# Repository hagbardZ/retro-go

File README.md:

# Table of contents
- [Description](#description)
- [Installation](#installation)
- [Usage](#usage)
- [Issues](#issues)
- [Development](#development)
- [Acknowledgements](#acknowledgements)
- [License](#license)

# Description
Retro-Go is a firmware to play retro games on ESP32-based devices (officially supported are
ODROID-GO and MRGC-G32, check [this list for other devices](components/retro-go/README.md)).
The project consists of a launcher and half a dozen applications that have been heavily
optimized to reduce their cpu, memory, and flash needs without reducing compatibility!

### Supported systems:
- Nintendo: **NES, SNES (slow), Gameboy, Gameboy Color, Game & Watch**, **Gameboy Advance**
- Sega: **SG-1000, Master System, Mega Drive / Genesis, Game Gear**
- Coleco: **Colecovision**
- NEC: **PC Engine**
- Atari: **Lynx**, **Atari 2600**
- Others: **DOOM** (including mods!), **Commodore 64**, **Commodore Amiga**, **Duke Nukem 3D**, **Quake**, **MSX**, **Tomb Raider**, **Super Mario 64**, **Outrun**, **Classicube**, **Open Tyrian**, **Playstation**, **Mario Kart 64**, **Quake 2**, **MP3 Player**, **Celeste**

### Retro-Go features:
- In-game menu
- Favorites and recently played
- GB color palettes, RTC adjust and save
- NES color palettes, PAL roms, NSF support
- More emulators and applications
- Scaling and filtering options
- Better performance and compatibility
- Turbo Speed/Fast forward
- Customizable launcher
- Cover art and save state previews
- Multiple save slots per game
- Wifi file manager
- And more!

### Screenshots

# Installation

### ODROID-GO
  1. Download `retro-go_1.x_odroid-go.fw` from the [release page](https://github.com/ducalex/retro-go/releases/) and copy it to `/odroid/firmware` on your sdcard.
  2. Power up the device while holding down B.
  3. Select retro-go in the files list and flash it.

### MyRetroGameCase G32 (GBC)
  1. Download `retro-go_1.x_mrgc-g32.fw` from the [release page](https://github.com/ducalex/retro-go/releases/) and copy it to `/espgbc/firmware` on your sdcard.
  2. Power up the device while holding down MENU (the volume knob).
  3. Select retro-go in the files list and flash it.

### Other devices
  1. Download the .img for your device from the [release page](https://github.com/ducalex/retro-go/releases/).
  2. Connect your device to a computer with a USB cable.
  3. Flash the image with esptool:
     - [Command line](https://github.com/espressif/esptool/releases/): Run `esptool.py write_flash --flash_size detect 0x0 retro-go_*.img`
     - [Web version](https://espressif.github.io/esptool-js/): Connect your device, click Erase Flash, then select your .img file and set address to 0x0, finally click Program)

Your particular device may require extra steps (like holding a button during power up) or different esptool flags or a special cable. If the above steps fail, you might need to ask the manufacturer for instructions on how to flash new firmware!

If your device is not already supported or if a prebuilt version isn't available for it you can check the [development section](#Development) for more information on how to build for your device.

# Usage

## Game covers / artwork
Game covers should be placed in the `romart` folder at the base of your sd card. You can obtain a pre-made pack [here](https://github.com/ducalex/retro-go-covers). Retro-Go is also compatible with the older Go-Play romart pack.

You can add missing cover art by creating a PNG image (160x168, 8bit). Two naming schemes are supported:
- Filename-based: `/romart/nes/Super Mario.png` (notice the rom extension is *not* included)
- CRC32-based: `/romart/nes/A/ABCDE123.png` where `nes` is the same as the rom folder, and `ABCDE123` is the CRC32 of the game (press A -> Properties in the launcher to find it), and `A` is the first character of the CRC32

_Note: CRC32-based, which is what is used in the pre-made pack, is much slower than name-based! This type is useful because filenames vary greatly despite having identical CRCs, but if you generate your own art I suggest you use filename-based format and delete all CRC-based art from your SD Card to improve responsiveness._

## BIOS files
Some emulators support loading a BIOS. The files should be placed as follows:
- GB: `/retro-go/bios/gb_bios.bin`
- GBC: `/retro-go/bios/gbc_bios.bin`
- FDS: `/retro-go/bios/fds_bios.bin`
- MSX: In folder `/retro-go/bios/msx/` put: `MSX.ROM` `MSX2.ROM` `MSX2EXT.ROM` `MSX2P.ROM` `MSX2PEXT.ROM` `FMPAC.ROM` `DISK.ROM` `MSXDOS2.ROM` `PAINTER.ROM` `KANJI.ROM`

## Game & Watch
The roms must be packed with [LCD-Game-Shrinker](https://github.com/bzhxx/LCD-Game-Shrinker) and a tutorial can be [found here](https://gist.github.com/DNA64/16fed499d6bd4664b78b4c0a9638e4ef).

## Wifi
To use wifi you will need to create a `/retro-go/config/wifi.json` config file. You can define up to 4 different networks, then selectable in the menu. Its content should look like this:

````json
{
  "ssid0": "my-network",
  "password0": "my-password",
  "ssid1": "my-other-network",
  "password1": "my-password",
  "ssid2": "my-third-network",
  "password2": "my-password",
  "ssid3": "my-last-network",
  "password3": "my-password"
}
````

### Time synchronization
Time synchronization happens in the launcher immediately after a successful connection to the network.
This is done via NTP by contacting `pool.ntp.org` and cannot be disabled at this time.
Timezone can be configured in the launcher's options menu.

### File manager
You can find the IP of your device in the *about* menu of retro-go. Then on your PC navigate to
http://192.168.x.x/ to access the file manager.

## External DAC (headphones)

Retro-Go supports [the external DAC mod for the ODROID-GO](https://github.com/backofficeshow/odroid-go-audio-hat)
which allows high quality audio through headphones. You can switch to it in the menu `Audio Out: Ext DAC`.

<details>
  <summary>Pinout</summary>

  | GO PIN | PCM5102A PIN |
  |--------|---------|
  | 1 | GND |
  | 2 | - |
  | 3 | LCK |
  | 4 | DIN |
  | 5 | BCK |
  | 6 | VIN |
  | 7 | - |
  | 8 | - |
  | 9 | - |
  | 10 | - |
</details>

# Issues

### Black screen / Boot loops
Retro-Go typically detects and resolves application crashes and freezes automatically. However, if you do
get stuck in a boot loop, you can hold `DOWN` while powering up the device to return to the launcher.

### Sound quality
The volume isn't correctly attenuated on the GO, resulting in upper volume levels that are too loud and
lower levels that are distorted due to DAC resolution. A quick way to improve the audio is to cut one
of the speaker wire and add a `33 Ohm (or thereabout)` resistor in series. Soldering is better but not
required, twisting the wires tightly will work just fine.
[A more involved solution can be seen here.](https://wiki.odroid.com/odroid_go/silent_volume)
Alternatively you can use the headphones DAC mod mentioned earlier in this document.

### Game Boy SRAM *(aka Save/Battery/Backup RAM)*
In Retro-Go, save states will provide you with the best and most reliable save experience. That being said, please
read on if you need or want SRAM saves. The SRAM format is compatible with VisualBoyAdvance so it may be used to
import or export saves.

You can configure automatic SRAM saving in the options menu. A longer delay will reduce stuttering at the cost
of losing data when powering down too quickly. Also note that when *resuming* a game, Retro-Go will give priority
to a save state if present.

### ZIP files
Most Retro-Go applications now support ZIP files. ZIP archives should contain only one ROM file and nothing else. ZIP support also depends on available memory and larger ROMs may fail to load on some devices unfortunately.

# Development
If you wish to build or modify Retro-Go, you can find help in the following documents:

- Build instructions in [BUILDING.md](BUILDING.md)
- Theming instructions [THEMING.md](THEMING.md)
- Porting instructions in [PORTING.md](PORTING.md)
- Translating instructions in [LOCALIZATION.md](LOCALIZATION.md)

# Acknowledgements
- The NES/GBC/SMS emulators and base library were originally from the "Triforce" fork of the [official Go-Play firmware](https://github.com/othercrashoverride/go-play) by crashoverride, Nemo1984, and many others.
- The design of the launcher was originally inspired/copied from [pelle7's go-emu](https://github.com/pelle7/odroid-go-emu-launcher).
- PCE-GO is a fork of [HuExpress](https://github.com/kallisti5/huexpress) and [pelle7's port](https://github.com/pelle7/odroid-go-pcengine-huexpress/) was used as reference.
- The Lynx emulator is a port of [libretro-handy](https://github.com/libretro/libretro-handy).
- The SNES emulator is a port of [Snes9x 2005](https://github.com/libretro/snes9x2005).
- The DOOM engine is a port of [PrBoom 2.5.0](http://prboom.sourceforge.net/).
- The Genesis emulator is a port of [Gwenesis](https://github.com/bzhxx/gwenesis/) by bzhxx.
- The Game & Watch emulator is a port of [lcd-game-emulator](https://github.com/bzhxx/lcd-game-emulator) by bzhxx.
- The MSX emulator is a port of [fMSX](https://fms.komkon.org/fMSX/) by Marat Fayzullin.
- PNG support is provided by [lodepng](https://github.com/lvandeve/lodepng/).
- PCE cover art is from [Christian_Haitian](https://github.com/christianhaitian).
- Some icons from [Rokey](https://iconarchive.com/show/seed-icons-by-rokey.html).
- Background images from [es-theme-gbz35](https://github.com/rxbrad/es-theme-gbz35).
- Special thanks to [RGHandhelds](https://www.rghandhelds.com/) and [MyRetroGamecase](https://www.myretrogamecase.com/) for sending me a [G32](https://www.myretrogamecase.com/products/game-mini-g32-esp32-retro-gaming-console-1) device.
- The [ODROID-GO](https://forum.odroid.com/viewtopic.php?f=159&t=37599) community for encouraging the development of retro-go!

# License
Everything in this project is licensed under the [GPLv2 license](COPYING) with the exception of the following components:
- fmsx/components/fmsx (MSX Emulator, custom non-commercial license)
- handy-go/components/handy (Lynx emulator, zlib)

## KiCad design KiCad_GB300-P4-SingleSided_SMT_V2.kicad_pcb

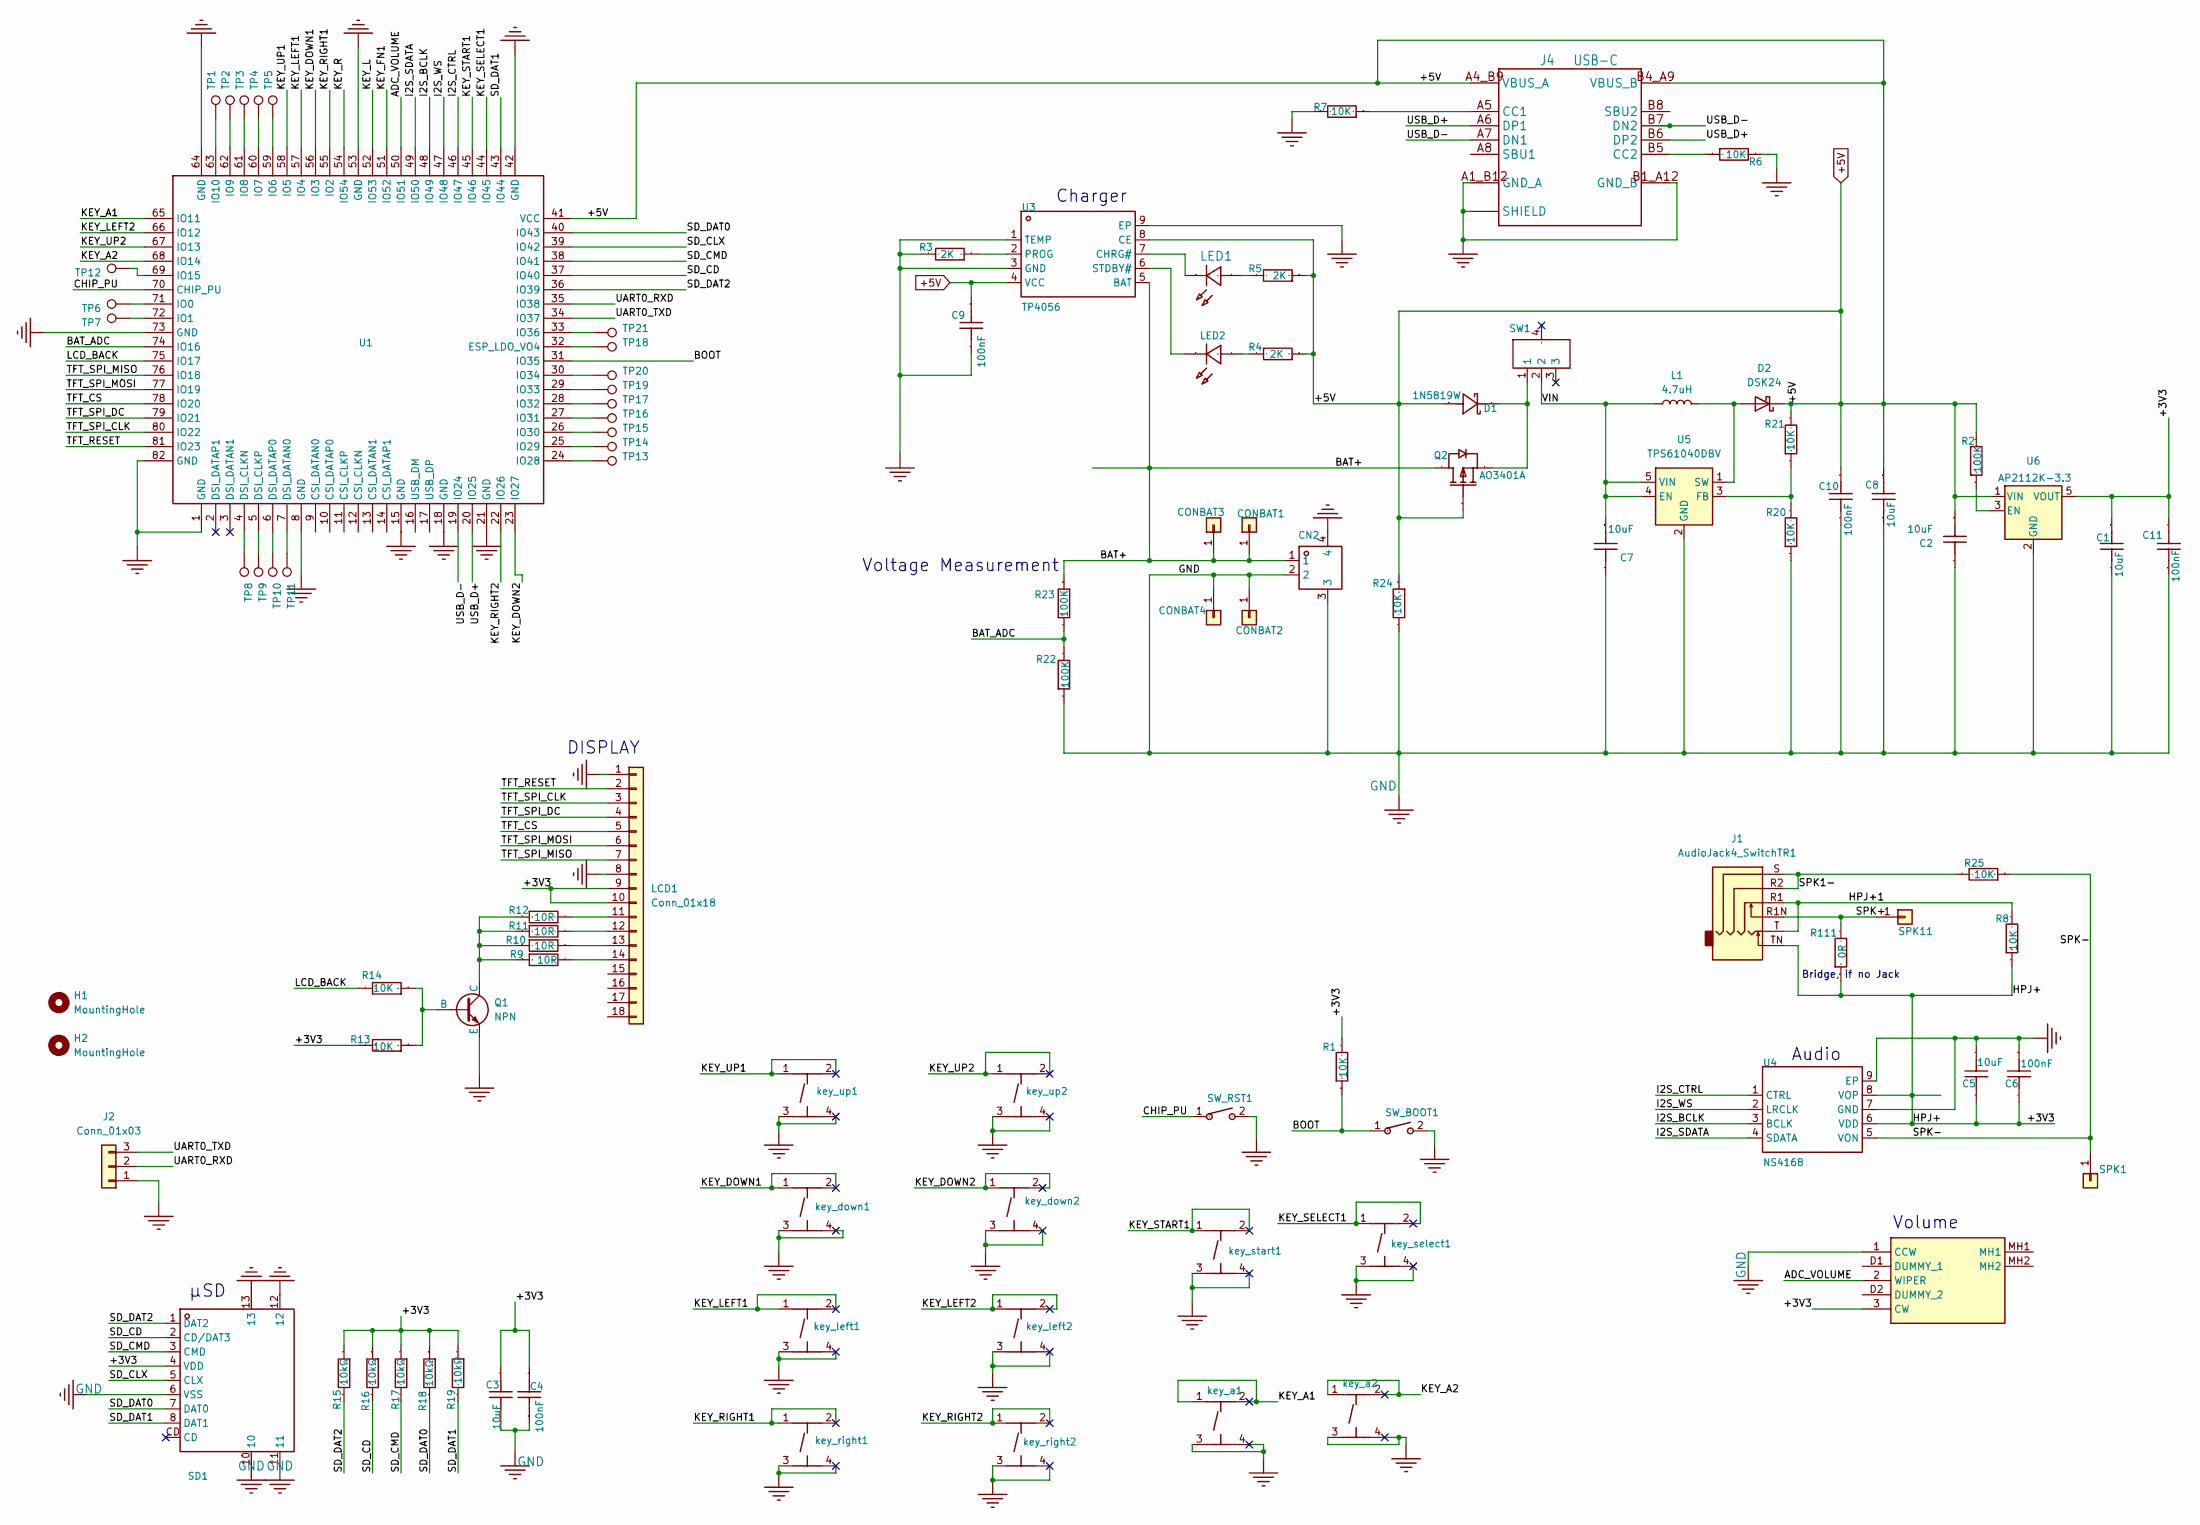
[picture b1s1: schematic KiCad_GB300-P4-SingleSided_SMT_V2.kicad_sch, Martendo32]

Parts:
C1, C2, C5: 10uF; 0603; Manufacturer Part CL10A106MA8NRNC; LCSC Part Name 10uF ±20% 25V
C3: 10uF; 0603; Manufacturer Part CGA0603X5R106K100JT; LCSC Part Name 10uF ±10% 10V
C4: 100nF; 0603; Manufacturer Part CGA0603X7R104K500JT; LCSC Part Name 100nF ±10% 50V
C6, C11: 100nF; 0603; Manufacturer Part CL10A106MA8NRNC; LCSC Part Name 10uF ±20% 25V
C7, C8: 10uF; 0603
C9, C10: 100nF; 0603
CN2: ZX-MX1.25-2PWT; CONN-SMD_2P-P1.25_D125F2W1-2W2P43; Manufacturer Part ZX-MX1.25-2PWT; LCSC Part Name 1x2P 间距:1.25mm 卧贴
CONBAT1, CONBAT2: Conn_01x01; PinHeader_1x01_P2.54mm_Vertical
CONBAT3, CONBAT4: Conn_01x01; TestPoint_Pad_3.0x3.0mm
D1: 1N5819W; SOD-123_L2.7-W1.6-LS3.7-RDaaa; Manufacturer Part 1N5819W; LCSC Part Name 电压:40V 电流:350mA
D2: DSK24; SOD-123FL_L2.7-W1.8-LS3.8-RD
H1, H2: MountingHole; MountingHole_5mm
J1: AudioJack4_SwitchTR1; AUDIO-SMD_HOOYA_PJ-242a
J2: Conn_01x03; PinSocket_1x03_P2.54mm_Vertical
J4: USB-C; AMPHENOL_GSB1C41110SSHR
L1: 4.7uH; IND-SMD_L2.5-W2.0_MHCH252012A
LCD1: Conn_01x18; ILI9341-2.8a
LED1: LED0603-RD_GREEN
LED2: LED0603-RD_RED
Q1: NPN; SOT-23-3_L2.9-W1.6-P1.90-LS2.8-BRaaa
Q2: AO3401A; SOT-23-3_L2.9-W1.6-P1.90-LS2.8-BR; Manufacturer Part AO3401A; LCSC Part Name P沟道 耐压:30V 电流:4A
R1, R6, R7, R8, R13, R14, R20, R21, R24, R25: 10K; 0603
R2, R22, R23: 100K; 0603
R3, R4, R5: 2K; 0603
R9, R10, R11, R12: 10R; 0603
R15, R16, R17, R18, R19: 10kΩ; 0603; Voltage-Supply(Max) 75V; Manufacturer Part 0603WAF1002T5E; LCSC Part Name 厚膜电阻 10kΩ ±1% 100mW
R111: 0R; 0603
SD1: TF-SMD_TF-01A; Manufacturer Part TF PUSH; LCSC Part Name 自弹式 MicroSD卡(TF卡) 卡座
SPK1, SPK11: Conn_01x01; TestPoint_Pad_D2.5mm
SW1: SK-3296S-01-L3; SW-SMD_MSK12C02-HB; Manufacturer Part SK-3296S-01-L3; LCSC Part Name 柄长2.5mm 卧贴双档 滑动开关
SW_BOOT1: 3*4 龟仔/微动/轻触开关; SW-SMD_L3.9-W3.0-P4.45; Manufacturer Part 3*4 龟仔/微动/轻触开关; LCSC Part Name 3*4 龟仔/微动/轻触开关
SW_RST1: 3*4 龟仔/微动/轻触开关; SW-SMD_L3.9-W3.0-P4.45; Manufacturer Part 3*4 龟仔/微动/轻触开关; LCSC Part Name 3*4 龟仔/微动/轻触开关
TP1, TP2, TP3, TP4, TP5, TP6, TP7, TP8, TP9, TP10, TP11, TP12, TP13, TP14, TP15, TP16, TP17, TP18, TP19, TP20, TP21: TestPoint; TestPoint_Pad_D1.0mm
U1: COMM-SMD_L25.0-W20.0-P1.00_WT0132P4-A1
U3: TP4056; ESOP-8_L4.9-W3.9-P1.27-LS6.0-BL-EP; Manufacturer Part TP4056; LCSC Part Name TP4056
U4: NS4168; ESOP-8_L4.9-W3.9-P1.27-LS6.0-BL-EP; Manufacturer Part NS4168; LCSC Part Name NS4168
U5: TPS61040DBV; SOT-23-5_L3.0-W1.7-P0.95-LS2.8-BR
U6: AP2112K-3.3; SOT-23-5_L2.9-W1.6-P0.95-LS2.8-BR
VR1: RK10J11E002Y; Manufacturer_Part_Number RK10J11E002Y; Mouser Part Number 688-RK10J11E002Y
key_a1: TS-1187A-B-A-B; 430451031836; Manufacturer Part TS-1187A-B-A-B; LCSC Part Name 5.1*5.1*1.5mm 立贴 轻触开关
key_a2: TS-1187A-B-A-B; DTSM-6; Manufacturer Part TS-1187A-B-A-B; LCSC Part Name 5.1*5.1*1.5mm 立贴 轻触开关
key_down1, key_down2: TS-1187A-B-A-B; 430451031836; Manufacturer Part TS-1187A-B-A-B; LCSC Part Name 5.1*5.1*1.5mm 立贴 轻触开关
key_left1, key_left2: TS-1187A-B-A-B; 430451031836; Manufacturer Part TS-1187A-B-A-B; LCSC Part Name 5.1*5.1*1.5mm 立贴 轻触开关
key_right1, key_right2: TS-1187A-B-A-B; 430451031836; Manufacturer Part TS-1187A-B-A-B; LCSC Part Name 5.1*5.1*1.5mm 立贴 轻触开关
key_select1: TS-1187A-B-A-B; 430451031836; Manufacturer Part TS-1187A-B-A-B; LCSC Part Name 5.1*5.1*1.5mm 立贴 轻触开关
key_start1: TS-1187A-B-A-B; 430451031836; Manufacturer Part TS-1187A-B-A-B; LCSC Part Name 5.1*5.1*1.5mm 立贴 轻触开关
key_up1, key_up2: TS-1187A-B-A-B; 430451031836; Manufacturer Part TS-1187A-B-A-B; LCSC Part Name 5.1*5.1*1.5mm 立贴 轻触开关

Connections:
+5V: C2.1, C8.1, C9.1, C10.1, D1.1 (A), D2.1 (K), J4.A4_B9 (VBUS_A), J4.B4_A9 (VBUS_B), Q2.1 (G), R2.2, R4.1, R5.1, R21.2, R24.1, U1.41 (VCC), U3.4 (VCC), U3.8 (CE), U6.1 (VIN)
/+3V3: C1.1, C3.2, C4.2, C5.2, C6.2, C11.2, J1.TN, LCD1.9, LCD1.10, R1.2, R8.1, R13.2, R15.1, R16.1, R17.1, R18.1, R19.1, R111.1, SD1.4 (VDD), U4.6 (VDD), U4.8 (VOP), U6.5 (VOUT), VR1.3 (CW)
/ADC_VOLUME: U1.50 (IO51), VR1.2 (WIPER)
/BAT+: CN2.1, CONBAT1.1, CONBAT3.1, Q2.3 (D), R23.1, U3.5 (BAT)
/BAT_ADC: R22.2, R23.2, U1.74 (IO16)
/BOOT: R1.1, SW_BOOT1.1, U1.31 (IO35)
/CHIP_PU: SW_RST1.1, U1.70 (CHIP_PU)
/HPJ+1: J1.R1, J1.T, R8.2
/I2S_BCLK: U1.48 (IO49), U4.3 (BCLK)
/I2S_CTRL: U1.46 (IO47), U4.1 (CTRL)
/I2S_SDATA: U1.49 (IO50), U4.4 (SDATA)
/I2S_WS: U1.47 (IO48), U4.2 (LRCLK)
/KEY_A1: U1.65 (IO11), key_a1.1 (A), key_a1.2 (B)
/KEY_A2: U1.68 (IO14), key_a2.1 (A), key_a2.2 (B)
/KEY_DOWN1: U1.56 (IO3), key_down1.1 (A), key_down1.2 (B)
/KEY_DOWN2: U1.23 (IO27), key_down2.1 (A), key_down2.2 (B)
/KEY_FN1: U1.51 (IO52)
/KEY_L: U1.52 (IO53)
/KEY_LEFT1: U1.57 (IO4), key_left1.1 (A), key_left1.2 (B)
/KEY_LEFT2: U1.66 (IO12), key_left2.1 (A), key_left2.2 (B)
/KEY_R: U1.54 (IO54)
/KEY_RIGHT1: U1.55 (IO2), key_right1.1 (A), key_right1.2 (B)
/KEY_RIGHT2: U1.22 (IO26), key_right2.1 (A), key_right2.2 (B)
/KEY_SELECT1: U1.44 (IO45), key_select1.1 (A), key_select1.2 (B)
/KEY_START1: U1.45 (IO46), key_start1.1 (A), key_start1.2 (B)
/KEY_UP1: U1.58 (IO5), key_up1.1 (A), key_up1.2 (B)
/KEY_UP2: U1.67 (IO13), key_up2.1 (A), key_up2.2 (B)
/LCD_BACK: R14.2, U1.75 (IO17)
/SD_CD: R16.2, SD1.2 (CD/DAT3), U1.37 (IO40)
/SD_CLX: SD1.5 (CLX), U1.39 (IO42)
/SD_CMD: R17.2, SD1.3 (CMD), U1.38 (IO41)
/SD_DAT0: R18.2, SD1.7 (DAT0), U1.40 (IO43)
/SD_DAT1: R19.2, SD1.8 (DAT1), U1.43 (IO44)
/SD_DAT2: R15.2, SD1.1 (DAT2), U1.36 (IO39)
/SPK1-: J1.R2, J1.S, R25.2
/SPK+: J1.R1N, R111.2, SPK11.1
/SPK-: R25.1, SPK1.1, U4.5 (VON)
/TFT_CS: LCD1.5, U1.78 (IO20)
/TFT_RESET: LCD1.2, U1.81 (IO23)
/TFT_SPI_CLK: LCD1.3, U1.80 (IO22)
/TFT_SPI_DC: LCD1.4, U1.79 (IO21)
/TFT_SPI_MISO: LCD1.7, U1.76 (IO18)
/TFT_SPI_MOSI: LCD1.6, U1.77 (IO19)
/UART0_RXD: J2.2, U1.35 (IO38)
/UART0_TXD: J2.3, U1.34 (IO37)
/USB_D+: J4.A6 (DP1), J4.B6 (DP2), U1.20 (IO25)
/USB_D-: J4.A7 (DN1), J4.B7 (DN2), U1.19 (IO24)
/VIN: C7.1, L1.1, SW1.2, U5.4 (EN), U5.5 (VIN)
GND: C1.2, C2.2, C3.1, C4.1, C5.1, C6.1, C7.2, C8.2, C9.2, C10.2, C11.1, CN2.2, CN2.3, CN2.4, CONBAT2.1, CONBAT4.1, J2.1, J4.A1_B12 (GND_A), J4.B1_A12 (GND_B), J4.SH1 (SHIELD), J4.SH2 (SHIELD), J4.SH3 (SHIELD), J4.SH4 (SHIELD), LCD1.1, LCD1.8, Q1.3 (E), R3.2, R6.2, R7.2, R20.1, R22.1, R24.2, SD1.6 (VSS), SD1.10, SD1.11, SD1.12, SD1.13, SW_BOOT1.2, SW_RST1.2, U1.1 (GND), U1.8 (GND), U1.15 (GND), U1.18 (GND), U1.21 (GND), U1.42 (GND), U1.53 (GND), U1.64 (GND), U1.73 (GND), U1.82 (GND), U3.1 (TEMP), U3.3 (GND), U3.9 (EP), U4.7 (GND), U4.9 (EP), U5.2 (GND), U6.2 (GND), VR1.1 (CCW), key_a1.3 (C), key_a1.4 (D), key_a2.3 (C), key_a2.4 (D), key_down1.3 (C), key_down1.4 (D), key_down2.3 (C), key_down2.4 (D), key_left1.3 (C), key_left1.4 (D), key_left2.3 (C), key_left2.4 (D), key_right1.3 (C), key_right1.4 (D), key_right2.3 (C), key_right2.4 (D), key_select1.3 (C), key_select1.4 (D), key_start1.3 (C), key_start1.4 (D), key_up1.3 (C), key_up1.4 (D), key_up2.3 (C), key_up2.4 (D)
unnamed: D1.2 (C), Q2.2 (S), SW1.1
unnamed: D2.2 (A), L1.2, U5.1 (SW)
unnamed: J4.A5 (CC1), R7.1
unnamed: J4.B5 (CC2), R6.1
unnamed: LCD1.11, R12.2
unnamed: LCD1.12, R11.2
unnamed: LCD1.13, R10.2
unnamed: LCD1.14, R9.2
unnamed: LED1.2 (A), R5.2
unnamed: LED1.1 (C), U3.7 (CHRG#)
unnamed: LED2.2 (A), R4.2
unnamed: LED2.1 (C), U3.6 (STDBY#)
unnamed: Q1.2 (B), R13.1, R14.1
unnamed: Q1.1 (C), R9.1, R10.1, R11.1, R12.1
unnamed: TP8.1, U1.4 (DSI_CLKN)
unnamed: TP9.1, U1.5 (DSI_CLKP)
unnamed: TP11.1, U1.7 (DSI_DATAN0)
unnamed: TP10.1, U1.6 (DSI_DATAP0)
unnamed: TP18.1, U1.32 (ESP_LDO_VO4)
unnamed: TP6.1, U1.71 (IO0)
unnamed: TP7.1, U1.72 (IO1)
unnamed: TP5.1, U1.59 (IO6)
unnamed: TP4.1, U1.60 (IO7)
unnamed: TP3.1, U1.61 (IO8)
unnamed: TP2.1, U1.62 (IO9)
unnamed: TP1.1, U1.63 (IO10)
unnamed: TP12.1, U1.69 (IO15)
unnamed: TP13.1, U1.24 (IO28)
unnamed: TP14.1, U1.25 (IO29)
unnamed: TP15.1, U1.26 (IO30)
unnamed: TP16.1, U1.27 (IO31)
unnamed: TP17.1, U1.28 (IO32)
unnamed: TP19.1, U1.29 (IO33)
unnamed: TP20.1, U1.30 (IO34)
unnamed: TP21.1, U1.33 (IO36)
unnamed: R3.1, U3.2 (PROG)
unnamed: R20.2, R21.1, U5.3 (FB)
unnamed: R2.1, U6.3 (EN)

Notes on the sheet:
µSD
DISPLAY
Audio
Volume
Charger
Voltage Measurement
Bridge, if no Jack

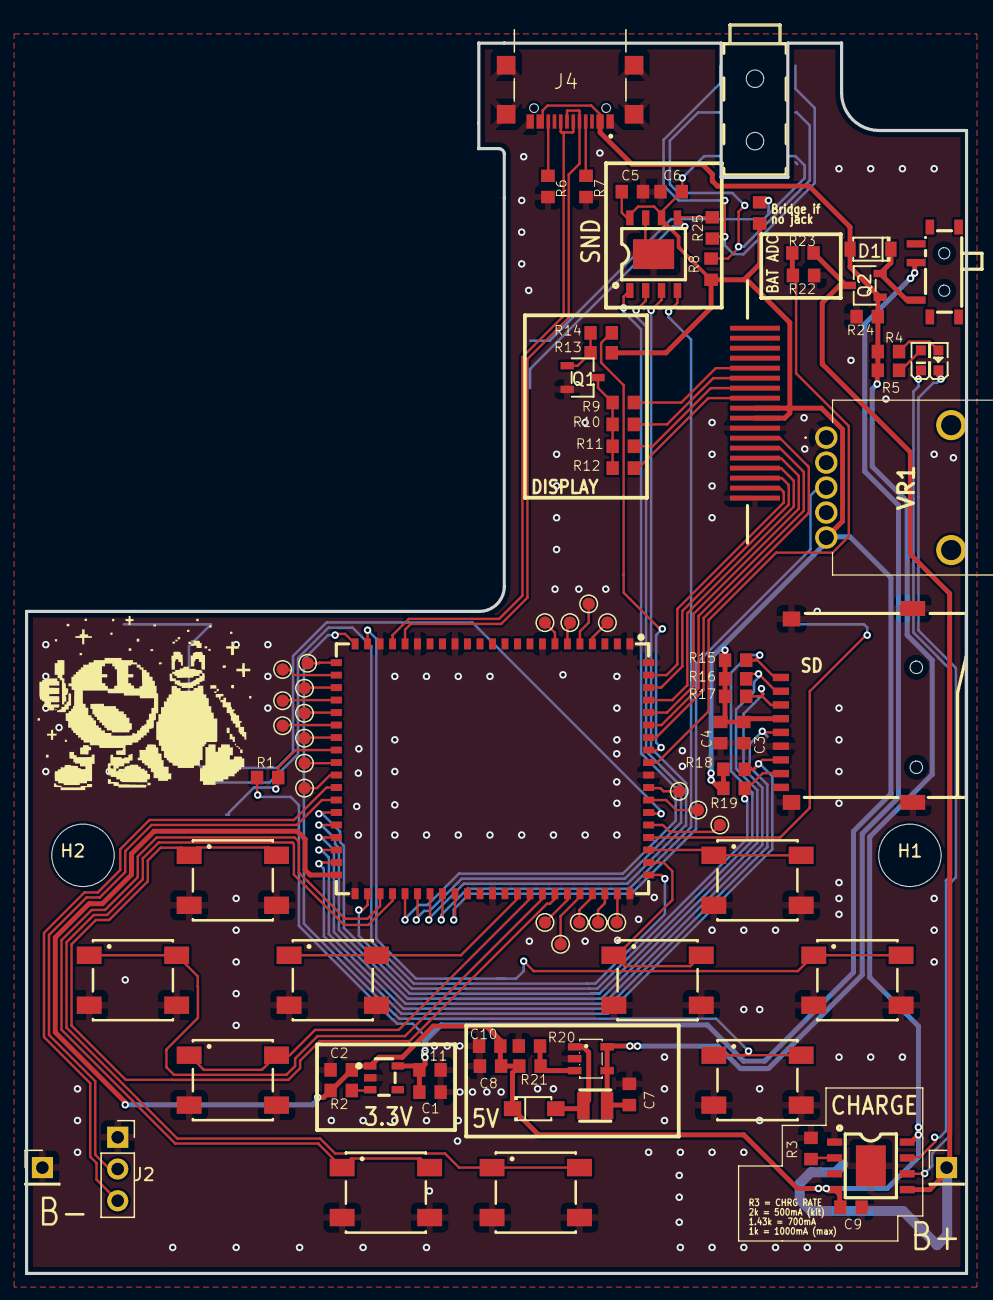
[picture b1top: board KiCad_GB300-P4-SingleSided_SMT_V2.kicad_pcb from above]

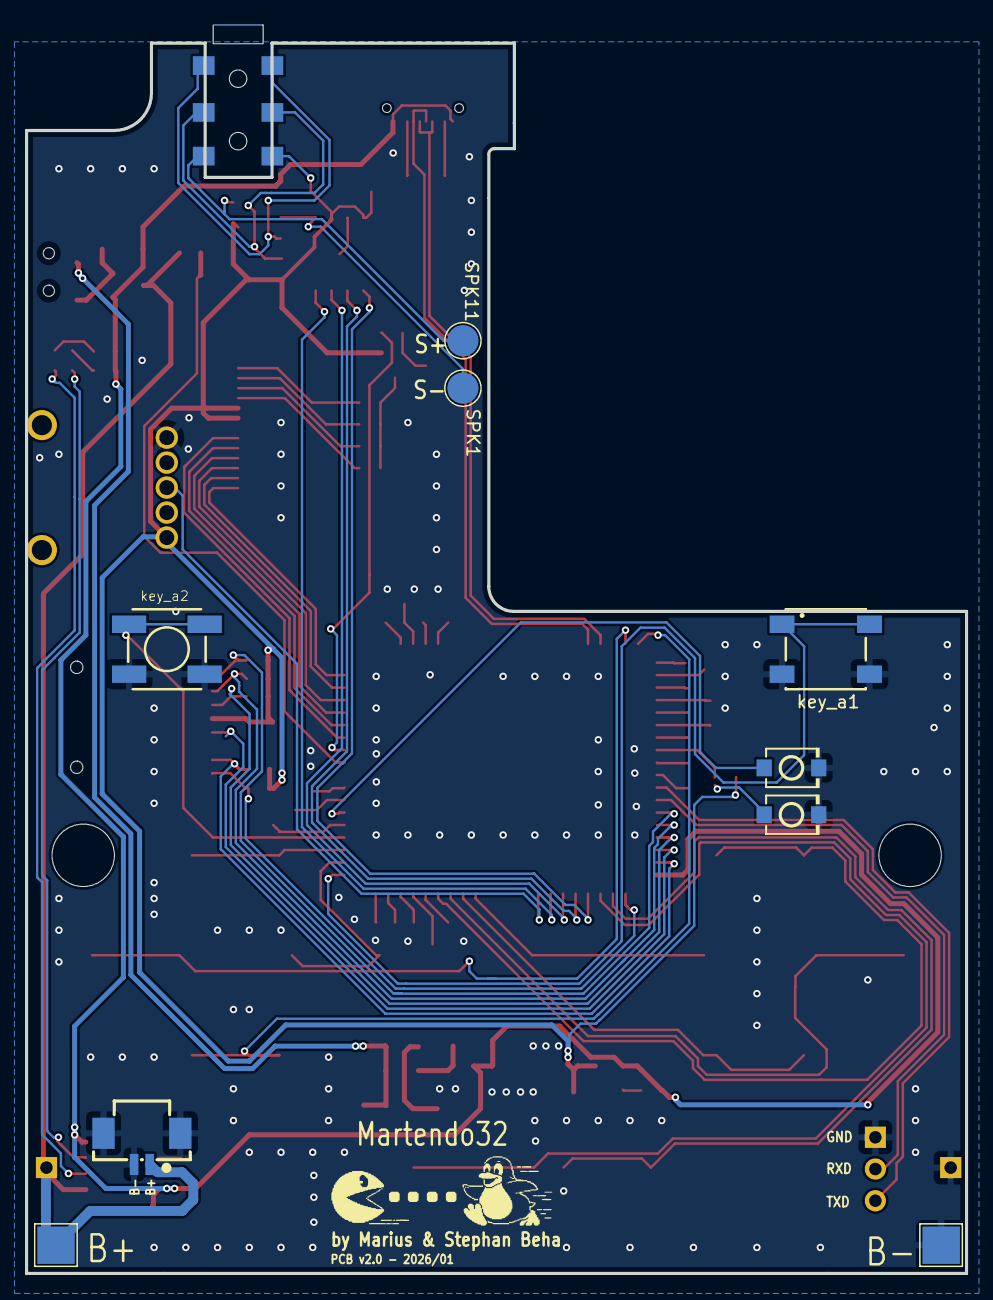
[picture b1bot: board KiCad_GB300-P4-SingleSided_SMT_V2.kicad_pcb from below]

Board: 2 copper layers, 75.2 x 99.9 mm, 100 parts (9 on the bottom side), 84 nets.

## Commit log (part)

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2026-04-23 bug2
2026-04-24 added quake
2026-04-24 added martendo targets
2026-04-24 minor changes
2026-04-27 updated stella (Atari)
2026-04-27 switched from lfs to regular files
2026-04-27 updated docs
2026-04-27 Update README.md
    updated docs
2026-04-27 Update README.md
    updated pictures in docs
2026-06-09 added bootstrapped
2026-06-27 added include dirent.h in global.c in duke3d to be compatible with v5.5.4, made everything linux compatible
